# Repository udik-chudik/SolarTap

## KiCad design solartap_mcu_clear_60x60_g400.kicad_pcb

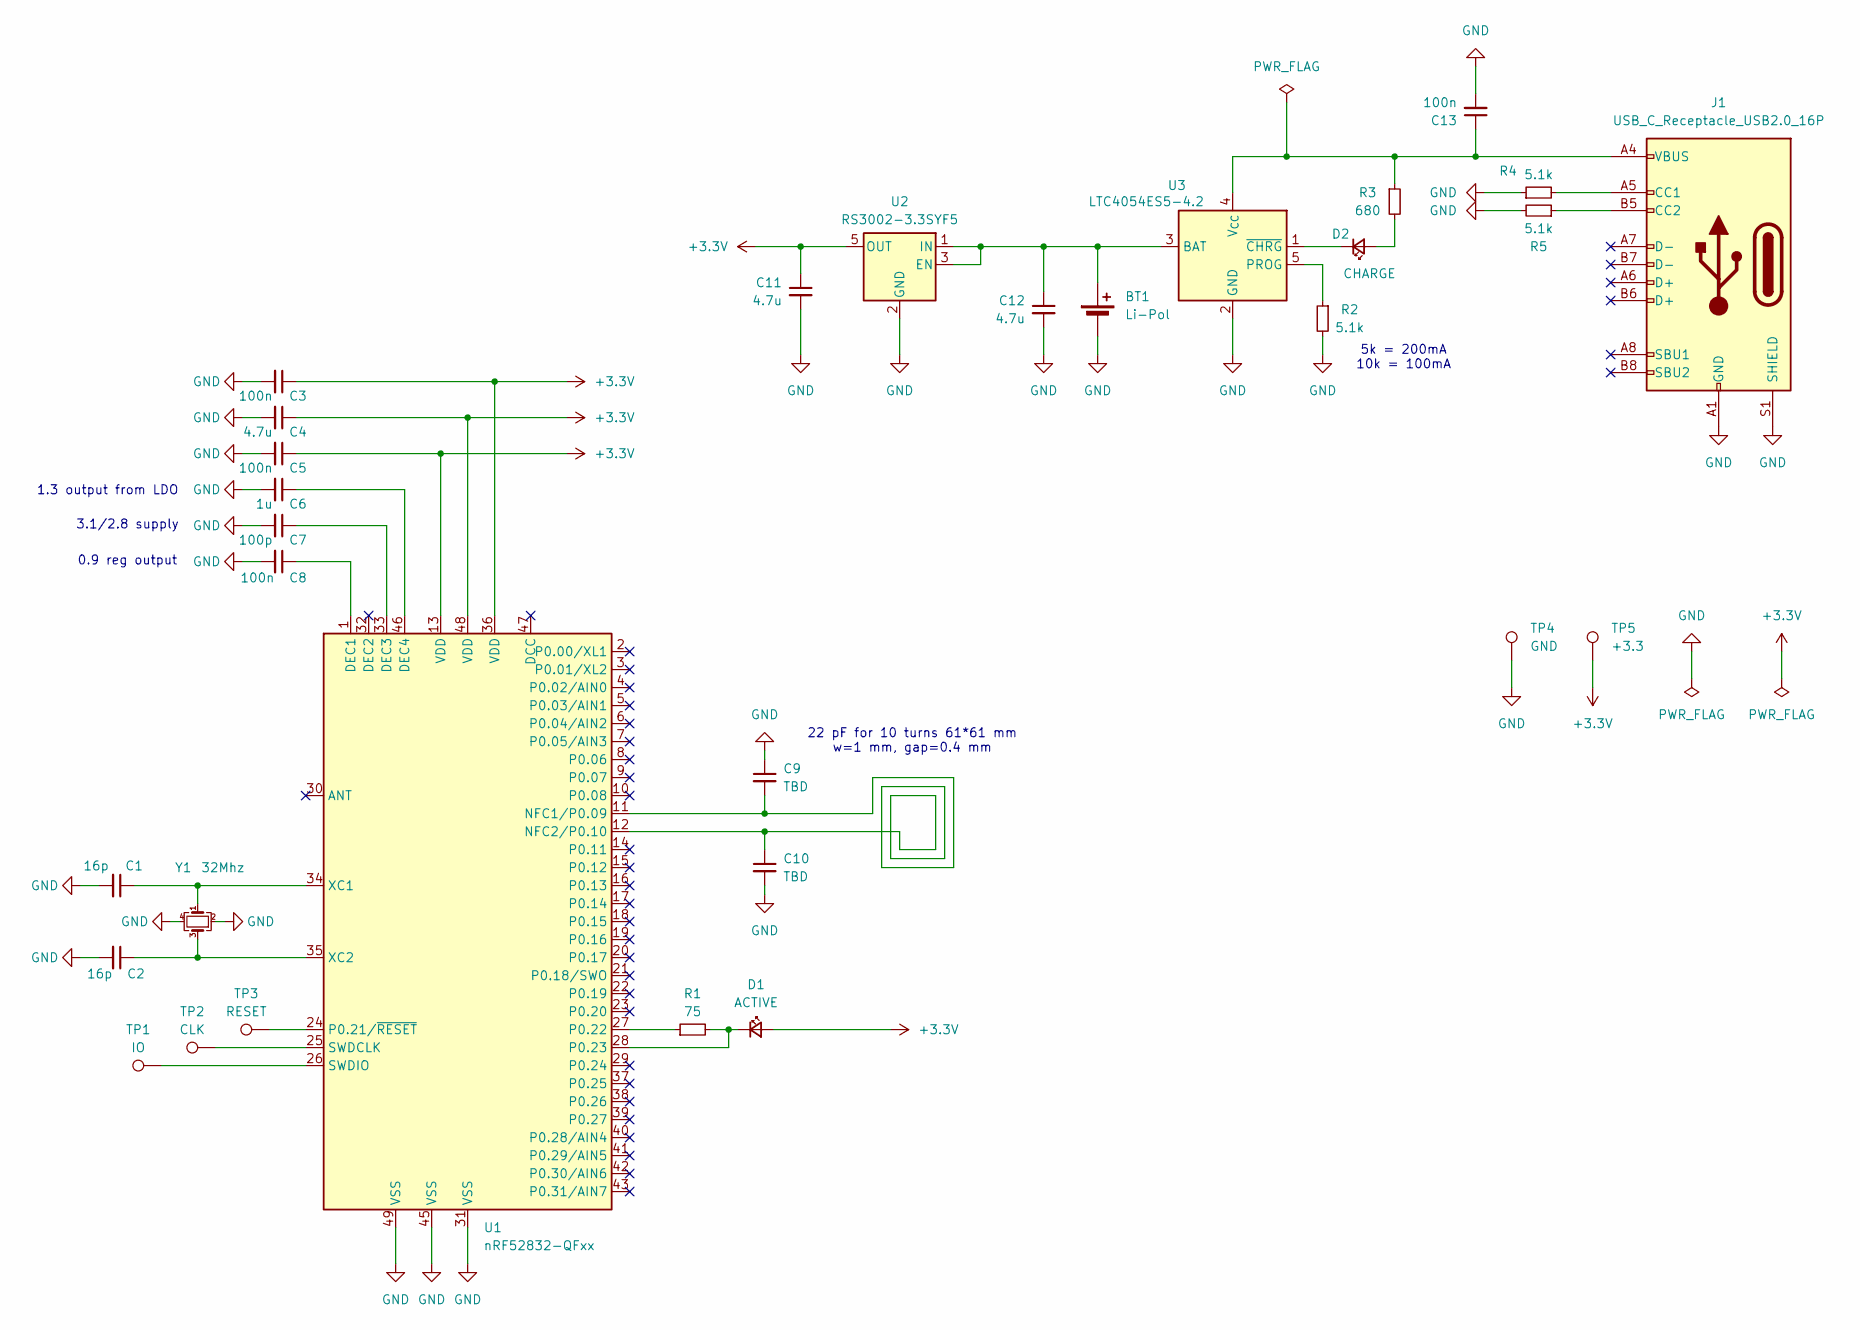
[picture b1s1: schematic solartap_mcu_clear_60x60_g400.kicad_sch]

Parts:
BT1: Li-Pol; li-pol
C1, C2: 16p; C_0805_2012Metric
C3, C5, C8, C13: 100n; C_0805_2012Metric
C4, C11, C12: 4.7u; C_0805_2012Metric
C6: 1u; C_0805_2012Metric
C7: 100p; C_0805_2012Metric
C9, C10: TBD; C_0805_2012Metric
D1: ACTIVE; LED_0805_2012Metric
D2: CHARGE; LED_0805_2012Metric
J1: USB_C_Receptacle_USB2.0_16P; USB_C_Receptacle_GCT_USB4105-xx-A_16P_TopMnt_Horizontal
R1: 75; R_0805_2012Metric
R2, R4, R5: 5.1k; R_0805_2012Metric
R3: 680; R_0805_2012Metric
TP1: IO; TestPoint_Keystone_5015_Micro-Minature
TP2: CLK; TestPoint_Keystone_5015_Micro-Minature
TP3: RESET; TestPoint_Keystone_5015_Micro-Minature
TP4: GND; TestPoint_Keystone_5015_Micro-Minature
TP5: +3.3; TestPoint_Keystone_5015_Micro-Minature
U1: nRF52832-QFxx; QFN-48-1EP_6x6mm_P0.4mm_EP4.6x4.6mm
U2: RS3002-3.3SYF5; SOT-23-5
U3: LTC4054ES5-4.2; TSOT-23-5
Y1: 32Mhz; Crystal_SMD_3225-4Pin_3.2x2.5mm

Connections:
+3.3V: C3.1, C4.1, C5.1, C11.1, D1.2 (A), TP5.1, U1.13 (VDD), U1.36 (VDD), U1.48 (VDD), U2.5 (OUT)
GND: BT1.2 (-), C1.2, C2.2, C3.2, C4.2, C5.2, C6.2, C7.2, C8.2, C9.1, C10.2, C11.2, C12.2, C13.2, J1.A1 (GND), J1.A12 (GND), J1.B1 (GND), J1.B12 (GND), J1.S1 (SHIELD), R2.2, R4.1, R5.2, TP4.1, U1.31 (VSS), U1.45 (VSS), U1.49 (VSS), U2.2 (GND), U3.2 (GND), Y1.2, Y1.4
unnamed: BT1.1 (+), C12.1, U2.1 (IN), U2.3 (EN), U3.3 (BAT)
unnamed: D1.1 (K), R1.2, U1.28 (P0.23)
unnamed: D2.2 (A), R3.2
unnamed: D2.1 (K), U3.1 (~CHRG)
unnamed: J1.A5 (CC1), R4.2
unnamed: J1.B5 (CC2), R5.1
unnamed: C8.1, U1.1 (DEC1)
unnamed: C7.1, U1.33 (DEC3)
unnamed: C6.1, U1.46 (DEC4)
unnamed: C9.2, C10.1, U1.11 (NFC1/P0.09), U1.12 (NFC2/P0.10)
unnamed: TP3.1, U1.24 (P0.21/~RESET)
unnamed: R1.1, U1.27 (P0.22)
unnamed: TP2.1, U1.25 (SWDCLK)
unnamed: TP1.1, U1.26 (SWDIO)
unnamed: C1.1, U1.34 (XC1), Y1.1
unnamed: C2.1, U1.35 (XC2), Y1.3
unnamed: R2.1, U3.5 (PROG)
unnamed: C13.1, J1.A4 (VBUS), J1.A9 (VBUS), J1.B4 (VBUS), J1.B9 (VBUS), R3.1, U3.4 (V_{CC})

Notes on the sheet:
0.9 reg output
1.3 output from LDO
22 pF for 10 turns 61*61 mm w=1 mm, gap=0.4 mm
5k = 200mA 10k = 100mA
3.1/2.8 supply

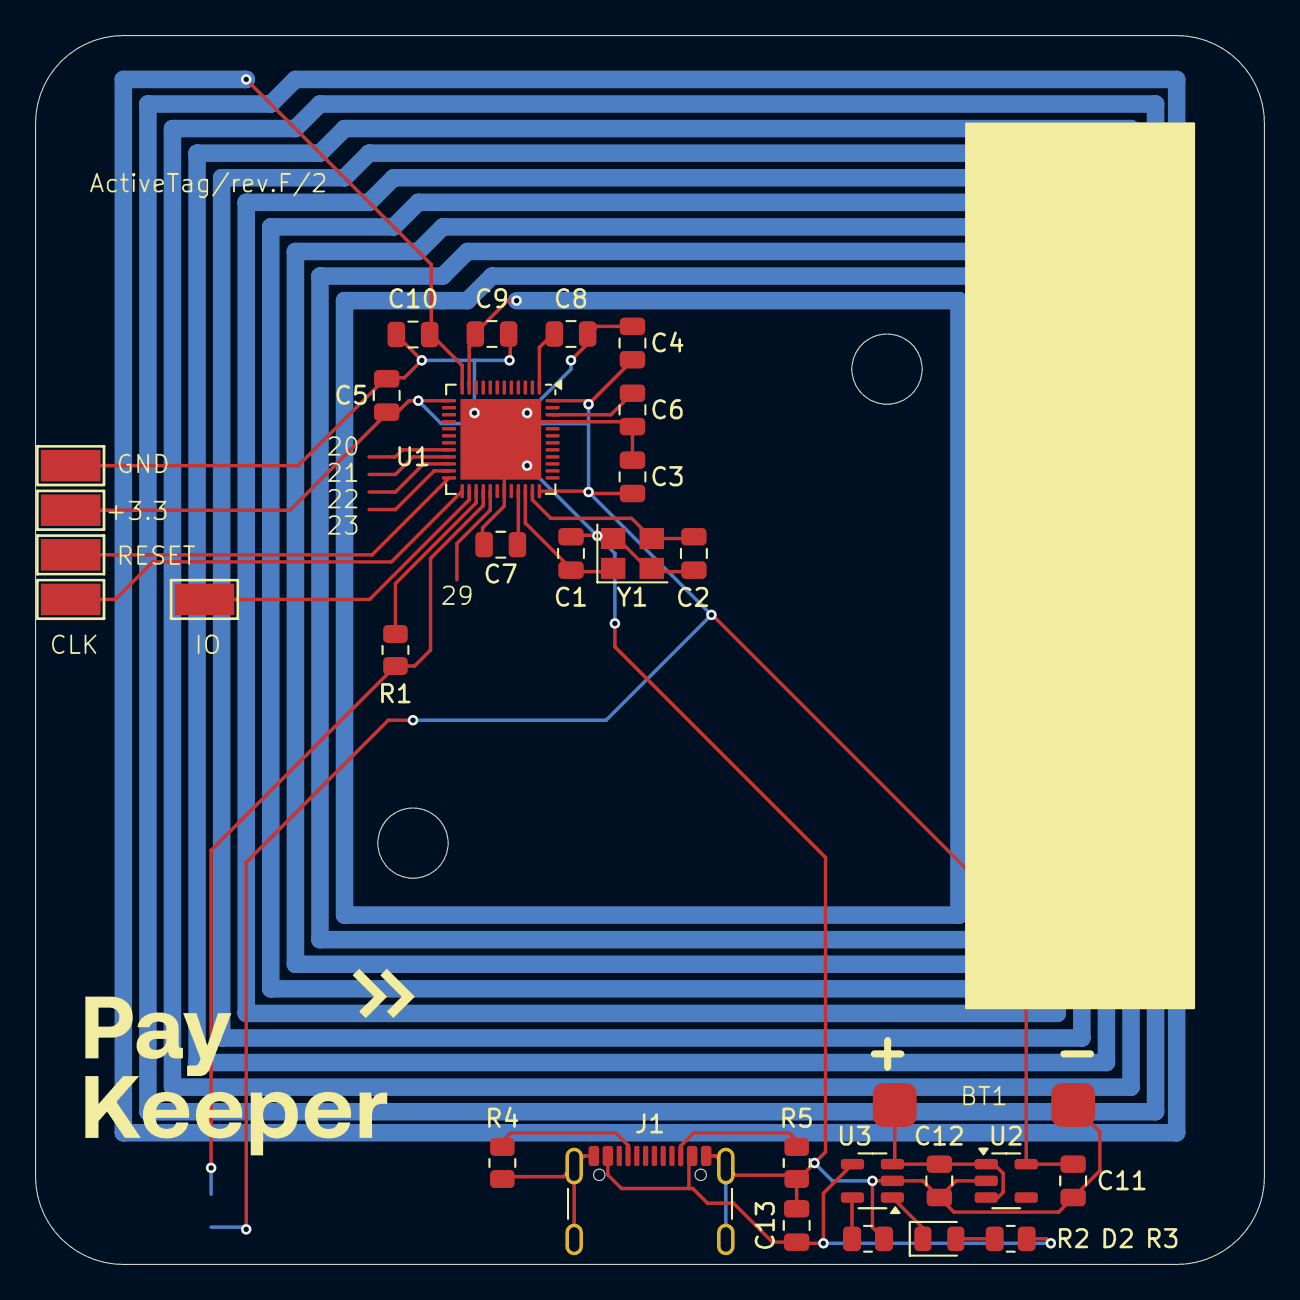
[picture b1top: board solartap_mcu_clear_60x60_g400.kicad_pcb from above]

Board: 2 copper layers, 70.0 x 70.0 mm, 31 parts (1 on the bottom side), 20 nets.

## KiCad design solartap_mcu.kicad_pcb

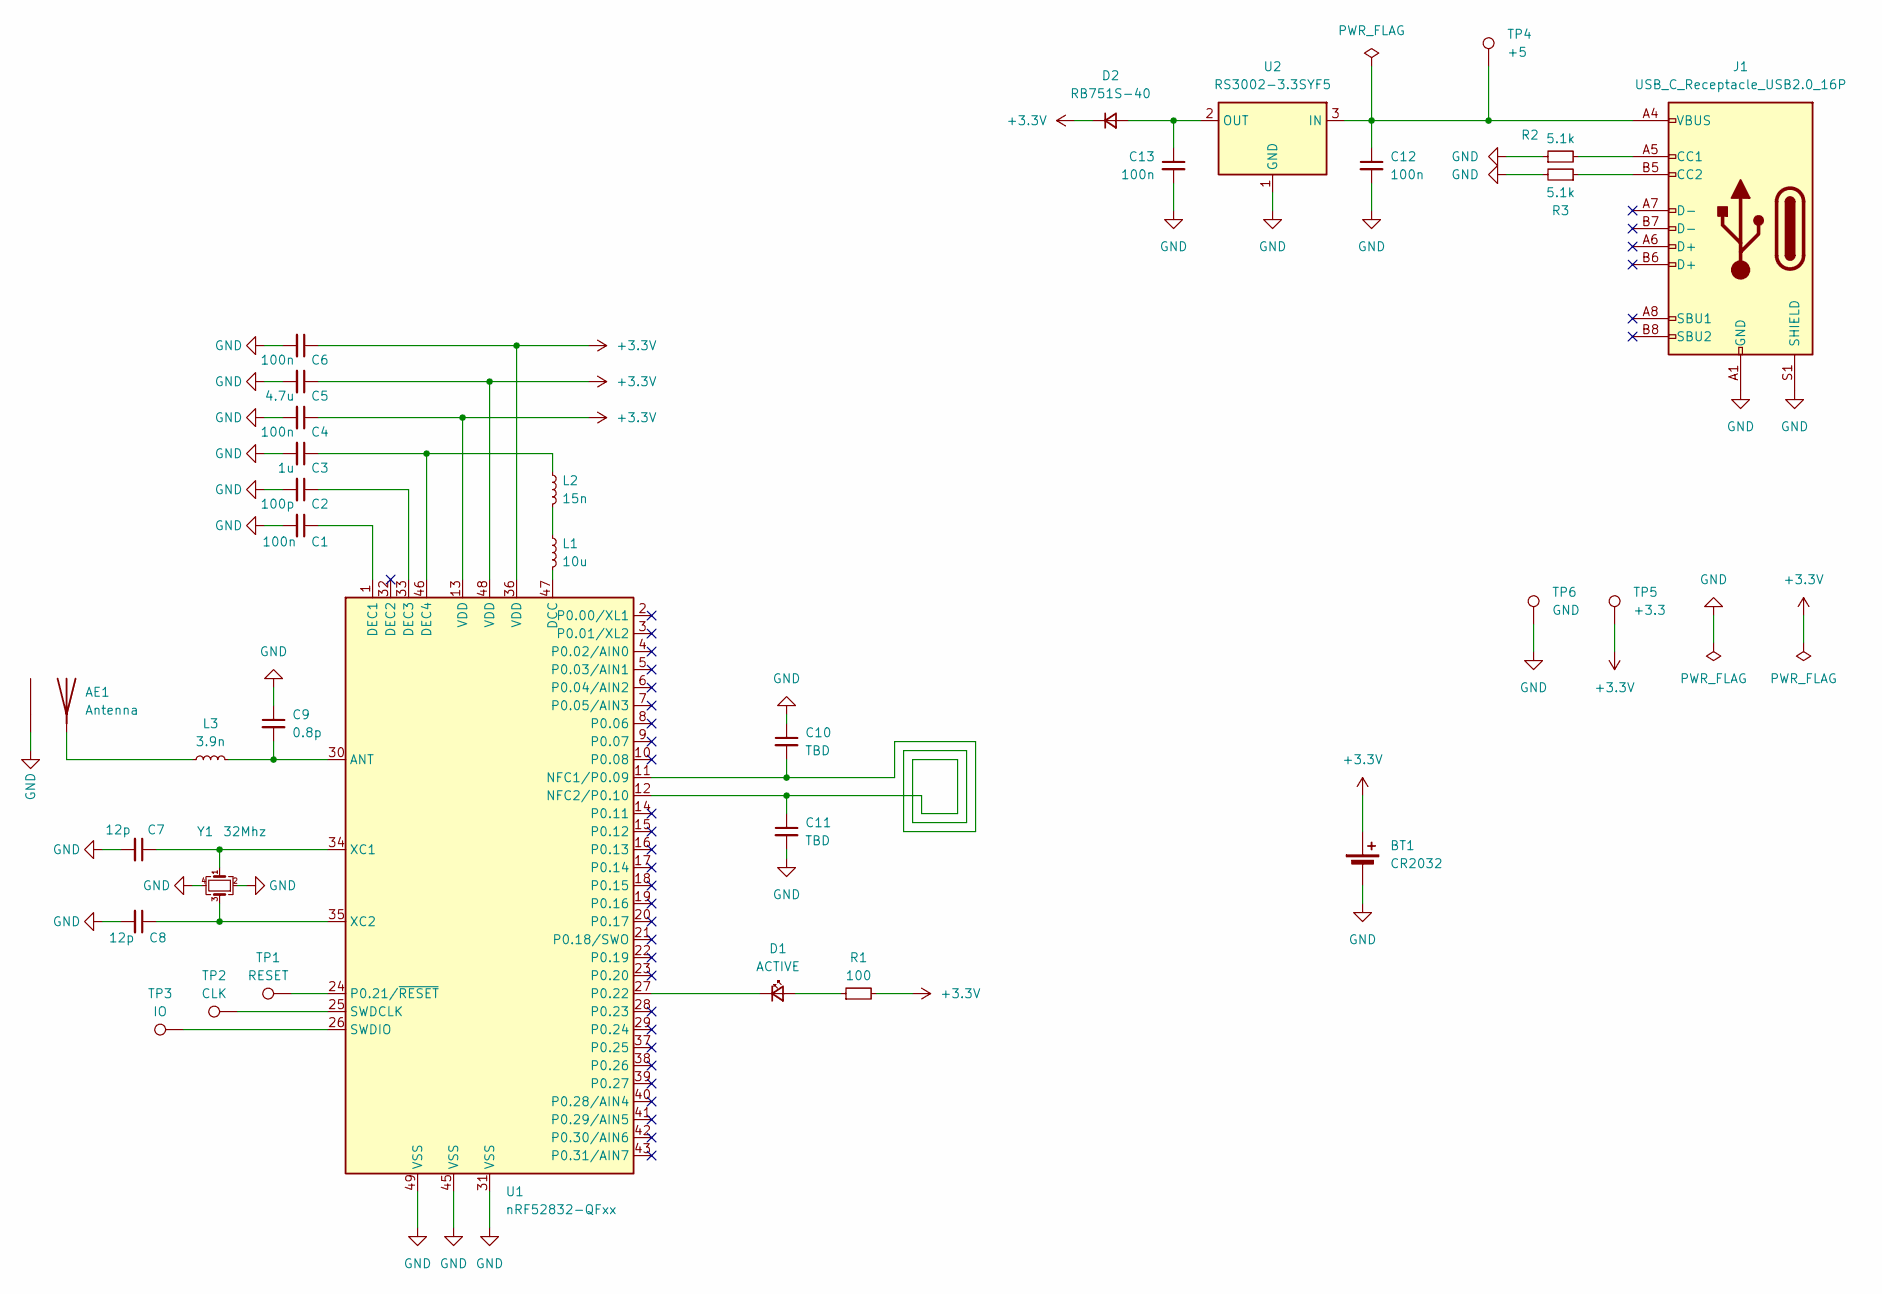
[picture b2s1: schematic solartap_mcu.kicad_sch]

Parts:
AE1: Antenna; Texas_SWRA117D_2.4GHz_Right
BT1: CR2032; BatteryHolder_MPD_BC2003_1x2032
C1, C4, C6, C12, C13: 100n; C_0805_2012Metric_Pad1.18x1.45mm_HandSolder
C2: 100p; C_0805_2012Metric_Pad1.18x1.45mm_HandSolder
C3: 1u; C_0805_2012Metric_Pad1.18x1.45mm_HandSolder
C5: 4.7u; C_0805_2012Metric_Pad1.18x1.45mm_HandSolder
C7, C8: 12p; C_0805_2012Metric_Pad1.18x1.45mm_HandSolder
C9: 0.8p; C_0805_2012Metric_Pad1.18x1.45mm_HandSolder
C10, C11: TBD; C_0805_2012Metric_Pad1.18x1.45mm_HandSolder
D1: ACTIVE; LED_0805_2012Metric
D2: RB751S-40; D_SOD-523
J1: USB_C_Receptacle_USB2.0_16P; USB_C_Receptacle_GCT_USB4110
L1: 10u; L_0805_2012Metric_Pad1.15x1.40mm_HandSolder
L2: 15n; L_0805_2012Metric_Pad1.15x1.40mm_HandSolder
L3: 3.9n; L_0805_2012Metric_Pad1.15x1.40mm_HandSolder
R1: 100; R_0805_2012Metric_Pad1.20x1.40mm_HandSolder
R2, R3: 5.1k; R_0805_2012Metric_Pad1.20x1.40mm_HandSolder
TP1: RESET; TestPoint_Pad_D3.0mm
TP2: CLK; TestPoint_Pad_D3.0mm
TP3: IO; TestPoint_Pad_D3.0mm
TP4: +5; TestPoint_Pad_D3.0mm
TP5: +3.3; TestPoint_Pad_D3.0mm
TP6: GND; TestPoint_Pad_D3.0mm
U1: nRF52832-QFxx; QFN-48-1EP_6x6mm_P0.4mm_EP4.6x4.6mm
U2: RS3002-3.3SYF5; SOT-23-3
Y1: 32Mhz; Crystal_SMD_3225-4Pin_3.2x2.5mm_HandSoldering

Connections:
+3.3V: BT1.1 (+), C4.1, C5.1, C6.1, D2.1 (K), R1.2, TP5.1, U1.13 (VDD), U1.36 (VDD), U1.48 (VDD)
GND: AE1. (gnd), BT1.2 (-), C1.2, C2.2, C3.2, C4.2, C5.2, C6.2, C7.2, C8.2, C9.1, C10.1, C11.2, C12.2, C13.2, J1.A1 (GND), J1.A12 (GND), J1.B1 (GND), J1.B12 (GND), J1.S1 (SHIELD), R2.1, R3.2, TP6.1, U1.31 (VSS), U1.45 (VSS), U1.49 (VSS), U2.1 (GND), Y1.2, Y1.4
unnamed: AE1.1 (A), L3.1
unnamed: D1.2 (A), R1.1
unnamed: D1.1 (K), U1.27 (P0.22)
unnamed: C13.1, D2.2 (A), U2.2 (OUT)
unnamed: J1.A5 (CC1), R2.2
unnamed: J1.B5 (CC2), R3.1
unnamed: L1.1, L2.2
unnamed: C9.2, L3.2, U1.30 (ANT)
unnamed: L1.2, U1.47 (DCC)
unnamed: C1.1, U1.1 (DEC1)
unnamed: C2.1, U1.33 (DEC3)
unnamed: C3.1, L2.1, U1.46 (DEC4)
unnamed: C10.2, C11.1, U1.11 (NFC1/P0.09), U1.12 (NFC2/P0.10)
unnamed: TP1.1, U1.24 (P0.21/~RESET)
unnamed: TP2.1, U1.25 (SWDCLK)
unnamed: TP3.1, U1.26 (SWDIO)
unnamed: C7.1, U1.34 (XC1), Y1.1
unnamed: C8.1, U1.35 (XC2), Y1.3
unnamed: C12.1, J1.A4 (VBUS), J1.A9 (VBUS), J1.B4 (VBUS), J1.B9 (VBUS), TP4.1, U2.3 (IN)

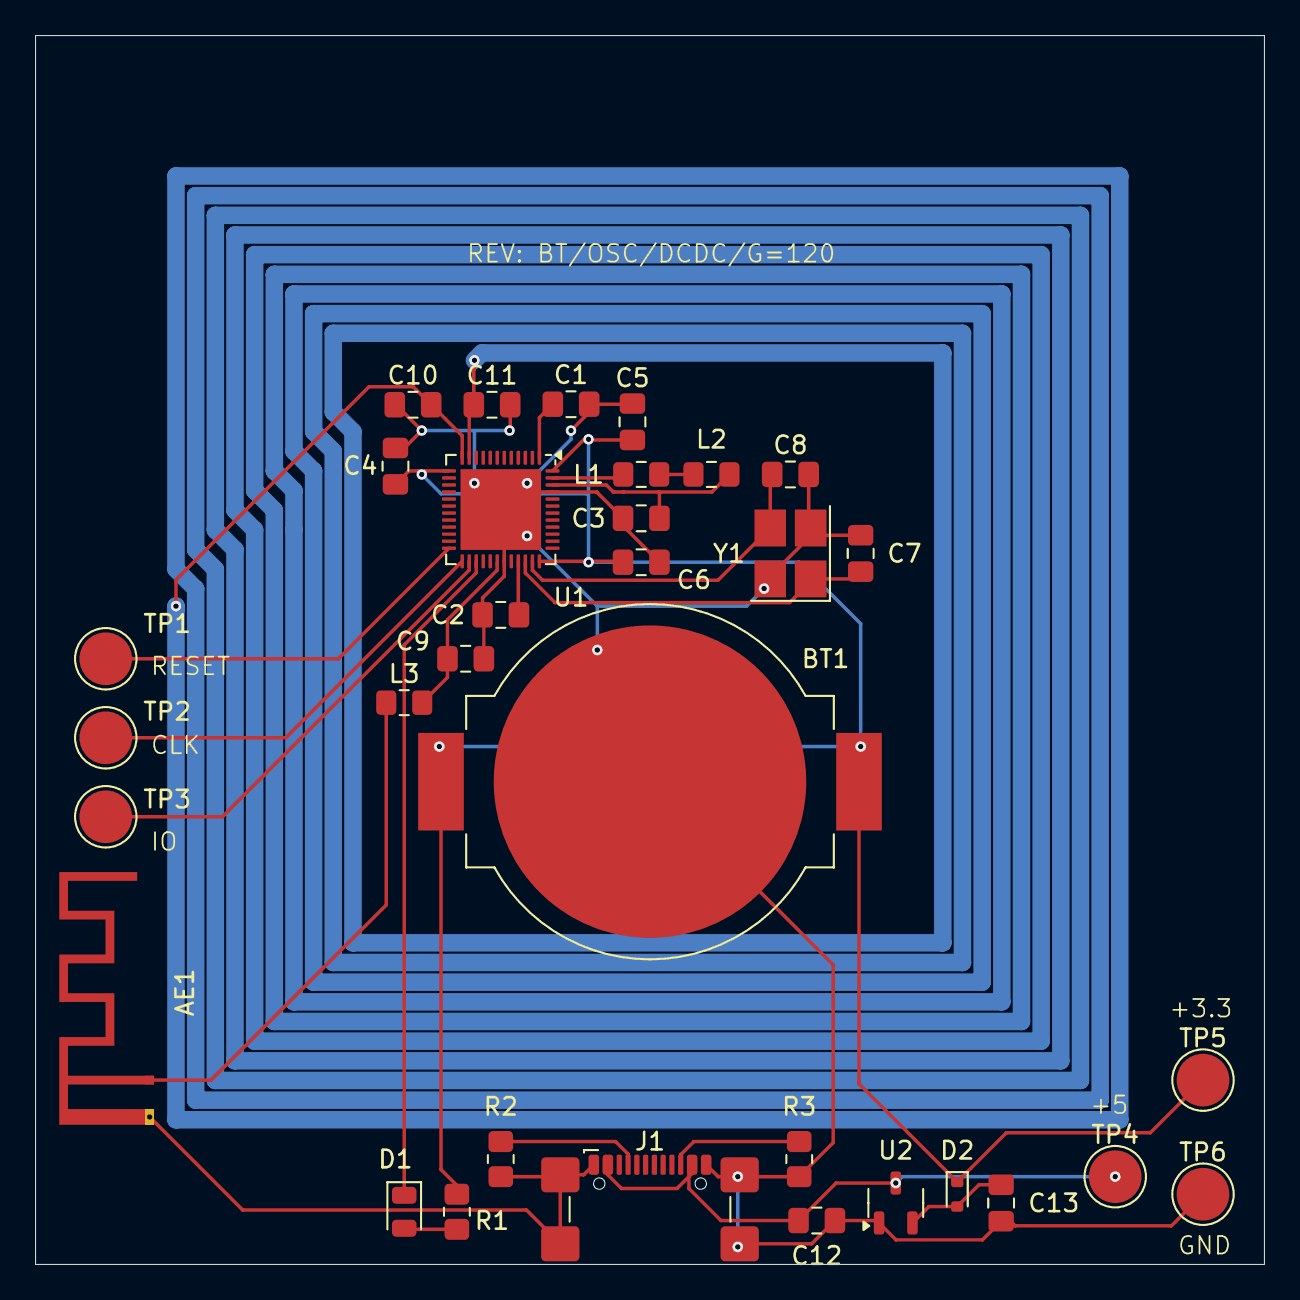
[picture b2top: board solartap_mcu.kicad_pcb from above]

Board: 2 copper layers, 70.0 x 70.0 mm, 33 parts (0 on the bottom side), 21 nets.

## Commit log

2024-10-15 Продовая версия без fiducials
2024-10-21 Добавили fiducials
2024-12-11 Переделали схему под аккомулятор + добавили его чарджер. rev.F
2025-07-17 Пожелания паши
2025-07-17 Нет маски над контактами для прошивки, С3 подальше от микрухи, отверсия 4 мм в диаметре
